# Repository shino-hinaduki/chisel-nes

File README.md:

Chisel NES

=======================

## Demo

TODO:

## HDL Design

TODO:

### 合成手順

#### ChiselNes.v の生成

以下のコマンドでscalaのprojectをビルドして、Chiselから生成したVerilog file  `dst/ChiselNes.v` を得る。

```shell
# sbtが使える環境の場合
$ sbt 'runMain top.ChiselNesDriver --target-dir dst'

# Docker
$ docker-compose run generate
```

#### DE0-CV向けにビルド

`eda/quartusprime_lite_21.1/chisel_nes.qpf` を Quartus Primeで開き、Compile Design を実行して論理合成した後、Program Deviceで書き込む。

(先の手順で生成した `dst/ChiselNes.v` がtop-level design entityに指定されており、プロジェクトにはその他IPや制約ファイルなどが含まれている)

## NES Peripheral EVB for DE0-CV

ファミコンエミュレータを実際のカートリッジで動作させる目的で設計した。

`eda/kicad_6.0.2/nes_peripheral` に、KiCADで設計した基板ファイルがあるので、こちらを参照。

### 機能概要

* DE0-CVのGPIO0,1に直結可能
  * ピンアサインを踏襲していれば、他評価ボード等でも利用可
  * GPIO1からカートリッジとのレベル変換回路をまとめてDisableにすることが可能
* カートリッジとの接続
  * 3.3V - 5V変換付き
  * レベル変換はすべて双方向のため、FPGA側をMaster/Slaveどちらでも利用可能
  * 周辺にプローブ用ピンも引き出し済
* 純正/互換コントローラ接続
  * 3.3V - 5V変換付き
* 純正回路と同じシフトレジスタICを用いたコントローラ入力
  * 3.3Vでプルアップされた入力回路とGNDを公開
  * 純正/互換コントローラの回路とは切替可
* MAX98537を使ったI2S-音声出力回路
* 5Vの外部供給

### ブロック図

```mermaid
graph LR
    GPIO--3.3V CPU/PPU Bus-->TXB0104PW_1
    GPIO--Output Enable-->OutputEnableSelect
    GPIO--5V-->5VSelect
    GPIO-->LED
    GPIO-->UserIO

    DC_Jack--5V-->5VSelect
    5VSelect--5V-->5V
    5V--5V-->CartridgeConnector

    OutputEnableSelect--Output Enable-->TXB0104PW_1
    TXB0104PW_1--5V CPU/PPU Bus-->CartridgeConnector

    GPIO--3.3V ShiftRegister I/O-->TXB0104PW_2
    JoyPadSerialSel-->TXB0104PW_2
    TXB0104PW_2--5V ShiftRegister I/O-->JoyPad0/1_Serial

    JoyPadParallelSel-->4021
    GPIO--3.3V ShiftRegister I/O-->4021
    4021--Parallel IO-->JoyPad0/1_Parallel

    GPIO--I2S-->MAX98357
    MAX98357--Audio Out-->Speaker
    GainSelect-->MAX98357
```

### 回路図

### 部品表

Digikeyで選定した部品を記載。チップコンデンサを始め、サイズ・機能互換であればこれに限らない。また、不要な回路は実装しなくても問題ない
ピンヘッダ、ピンソケットは2.54mm ピッチのものを別途準備すること。

| Ref | Value | 数量 | メーカ製品番号  | url |
| --- | ----  | ---- | --- | ---- |
| C1-C37 |0.1u	| 37 | CL10B104KB8NNWC | https://www.digikey.jp/ja/products/detail/samsung-electro-mechanics/CL10B104KB8NNWC/3887593 |
| C40 | 10p	| 1 | CL10C100CB8NNNC | https://www.digikey.jp/ja/products/detail/samsung-electro-mechanics/CL10C100CB8NNNC/3886727 |
| D1-D3 | LED	| 3 |5988070107F| https://www.digikey.jp/ja/products/detail/dialight/5988070107F/1291269 |
| F1 | Polyfuse_Small	| 1 |0603L300/9SLYR|https://www.digikey.jp/ja/products/detail/littelfuse-inc/0603L300-9SLYR/5427243|
| R1-R22 | 10k	| 22 |RC1608F103CS|https://www.digikey.jp/ja/products/detail/samsung-electro-mechanics/RC1608F103CS/3903493|
| R23	| 0	| 1 |RC0603FR-070RL|https://www.digikey.jp/ja/products/detail/yageo/RC0603FR-070RL/1304008|
| R25, R26 | 100k	| 2 |RC0603JR-07100KL|https://www.digikey.jp/ja/products/detail/yageo/RC0603JR-07100KL/726698|
| U1-U16 | TXB0104PW	| 16 |TXB0104PWR|https://www.digikey.jp/ja/products/detail/texas-instruments/TXB0104PWR/1629102|
| U17, U18 | 4021	| 2 |CD4021BMT|https://www.digikey.jp/ja/products/detail/texas-instruments/CD4021BMT/1690863|
| U19	| MAX98357 | 1 |MAX98357AETE+T|https://www.digikey.jp/ja/products/detail/analog-devices-inc-maxim-integrated/MAX98357AETE-T/4936122|

### GPIO Pin Assign

以下のピンアサインになっているためDE0-CVでなくとも利用可能。GPIO0側の5V,3.3Vは利用していない点に注意

#### GPIO0

|Pin#| GPIO#|KiCad SignalName| Description |
|----|------|----------------|-------------|
|  1 |   D0 |3V3_A11         | CPU Bus |
|  2 |   D1 |3V3_O2          | φ2, System Clock |
|  3 |   D2 |3V3_A10         | CPU Bus |
|  4 |   D3 |3V3_A12         | CPU Bus |
|  5 |   D3 |3V3_A7          | CPU Bus |
|  6 |   D5 |3V3_D7          | CPU Bus |
|  7 |   D6 |3V3_A6          | CPU Bus |
|  8 |   D7 |3V3_D6          | CPU Bus |
|  9 |   D8 |3V3_A3          | CPU Bus |
| 10 |   D9 |3V3_D3          | CPU Bus |
| 11 |   5V |NC              | GPIO0側は未使用 |
| 12 |  GND |GND             |  |
| 13 |  D10 |3V3_A2          | CPU Bus |
| 14 |  D11 |3V3_D2          | CPU Bus |
| 15 |  D12 |3V3_R/~W        | CPU Bus |
| 16 |  D13 |3V3_~ROMSEL     | CPU Bus |
| 17 |  D14 |3V3_~IRQ        | CPU Bus |
| 18 |  D15 |3V3_~WE         | PPU Bus |
| 19 |  D16 |3V3_PA6         | PPU Bus |
| 20 |  D17 |3V3_PA7         | PPU Bus |
| 21 |  D18 |3V3_PA5         | PPU Bus |
| 22 |  D19 |3V3_PA8         | PPU Bus |
| 23 |  D20 |3V3_PA2         | PPU Bus |
| 24 |  D21 |3V3_PA11        | PPU Bus |
| 25 |  D22 |3V3_PA1         | PPU Bus |
| 26 |  D23 |3V3_PA12        | PPU Bus |
| 27 |  D24 |3V3_PD1         | PPU Bus |
| 28 |  D25 |3V3_PD6         | PPU Bus |
| 29 | 3.3V |NC              | GPIO0側は未使用 |
| 30 |  GND |GND             |  |
| 31 |  D26 |3V3_PD2         | PPU Bus |
| 32 |  D27 |3V3_PD5         | PPU Bus |
| 33 |  D28 |3V3_JOY1_P/~S   | 1Player Controller |
| 34 |  D29 |3V3_JOY1_DO     | 1Player Controller |
| 35 |  D30 |3V3_JOY1_RSV    | 1Player Controller |
| 36 |  D31 |3V3_JOY1_CLK    | 1Player Controller |
| 37 |  D32 |3V3_I2S_BCLK    | Audio Codec |
| 38 |  D33 |3V3_I2S_LRCLK   | Audio Codec |
| 39 |  D34 |3V3_I2S_~SD_MODE| Audio Codec |
| 40 |  D35 |3V3_I2S_DIN     | Audio Codec |

#### GPIO1

|Pin#| GPIO#|KiCad SignalName| Description |
|----|------|----------------|-------------|
|  1 |   D0 |3V3_A9          | CPU Bus |
|  2 |   D1 |3V3_A13         | CPU Bus |
|  3 |   D2 |3V3_A8          | CPU Bus |
|  4 |   D3 |3V3_A14         | CPU Bus |
|  5 |   D3 |3V3_A5          | CPU Bus |
|  6 |   D5 |3V3_D5          | CPU Bus |
|  7 |   D6 |3V3_A4          | CPU Bus |
|  8 |   D7 |3V3_D4          | CPU Bus |
|  9 |   D8 |3V3_A1          | CPU Bus |
| 10 |   D9 |3V3_D1          | CPU Bus |
| 11 |   5V |BOARD_5V        | J8 CONN_5VSEL次第で使用する |
| 12 |  GND |GND             |  |
| 13 |  D10 |3V3_A0          | CPU Bus |
| 14 |  D11 |3V3_D0          | CPU Bus |
| 15 |  D12 |3V3_~RD         | PPU Bus |
| 16 |  D13 |3V3_~VRAMCS     | PPU Bus |
| 17 |  D14 |3V3_VRAMA10     | PPU Bus |
| 18 |  D15 |3V3_~PA13       | PPU Bus |
| 19 |  D16 |3V3_PA4         | PPU Bus |
| 20 |  D17 |3V3_PA9         | PPU Bus |
| 21 |  D18 |3V3_PA3         | PPU Bus |
| 22 |  D19 |3V3_PA10        | PPU Bus |
| 23 |  D20 |3V3_PA0         | PPU Bus |
| 24 |  D21 |3V3_PA13        | PPU Bus |
| 25 |  D22 |3V3_PD0         | PPU Bus |
| 26 |  D23 |3V3_PD7         | PPU Bus |
| 27 |  D24 |3V3_PD3         | PPU Bus |
| 28 |  D25 |3V3_PD4         | PPU Bus |
| 29 | 3.3V |3.3V            |  |
| 30 |  GND |GND             |  |
| 31 |  D26 |3V3_RSV0        | 5V側で取り出し可能 |
| 32 |  D27 |3V3_RSV1        | 5V側で取り出し可能 |
| 33 |  D28 |USER_GPIO1      | ピンソケットJ1に引き出し済 |
| 34 |  D29 |USER_LED        | OnBoard LED |
| 35 |  D30 |3V3_JOY2_MICIN  | 2Player Controller |
| 36 |  D31 |USER_GPIO0      | ピンソケットJ1に引き出し済 |
| 37 |  D32 |3V3_JOY2_DO     | 2Player Controller |
| 38 |  D33 |3V3_JOY2_CLK    | 2Player Controller |
| 39 |  D34 |3V3_JOY2_P/~S  | 2Player Controller |
| 40 |  D35 |3V3_OE_IN       | Lowの間はレベル変換をHi-Zで切り離せる |

### 設計データの活用範囲

`eda/kicad_6.0.2/nes_peripheral` にある基板設計データは、 [CC BY-NC 4.0](https://creativecommons.org/licenses/by-nc/4.0/deed) の範囲で利用を許可する。

例えば、本基板の設計データか内容を改変したデータを用い、製造した製品を営利目的で販売する行為は禁止である。

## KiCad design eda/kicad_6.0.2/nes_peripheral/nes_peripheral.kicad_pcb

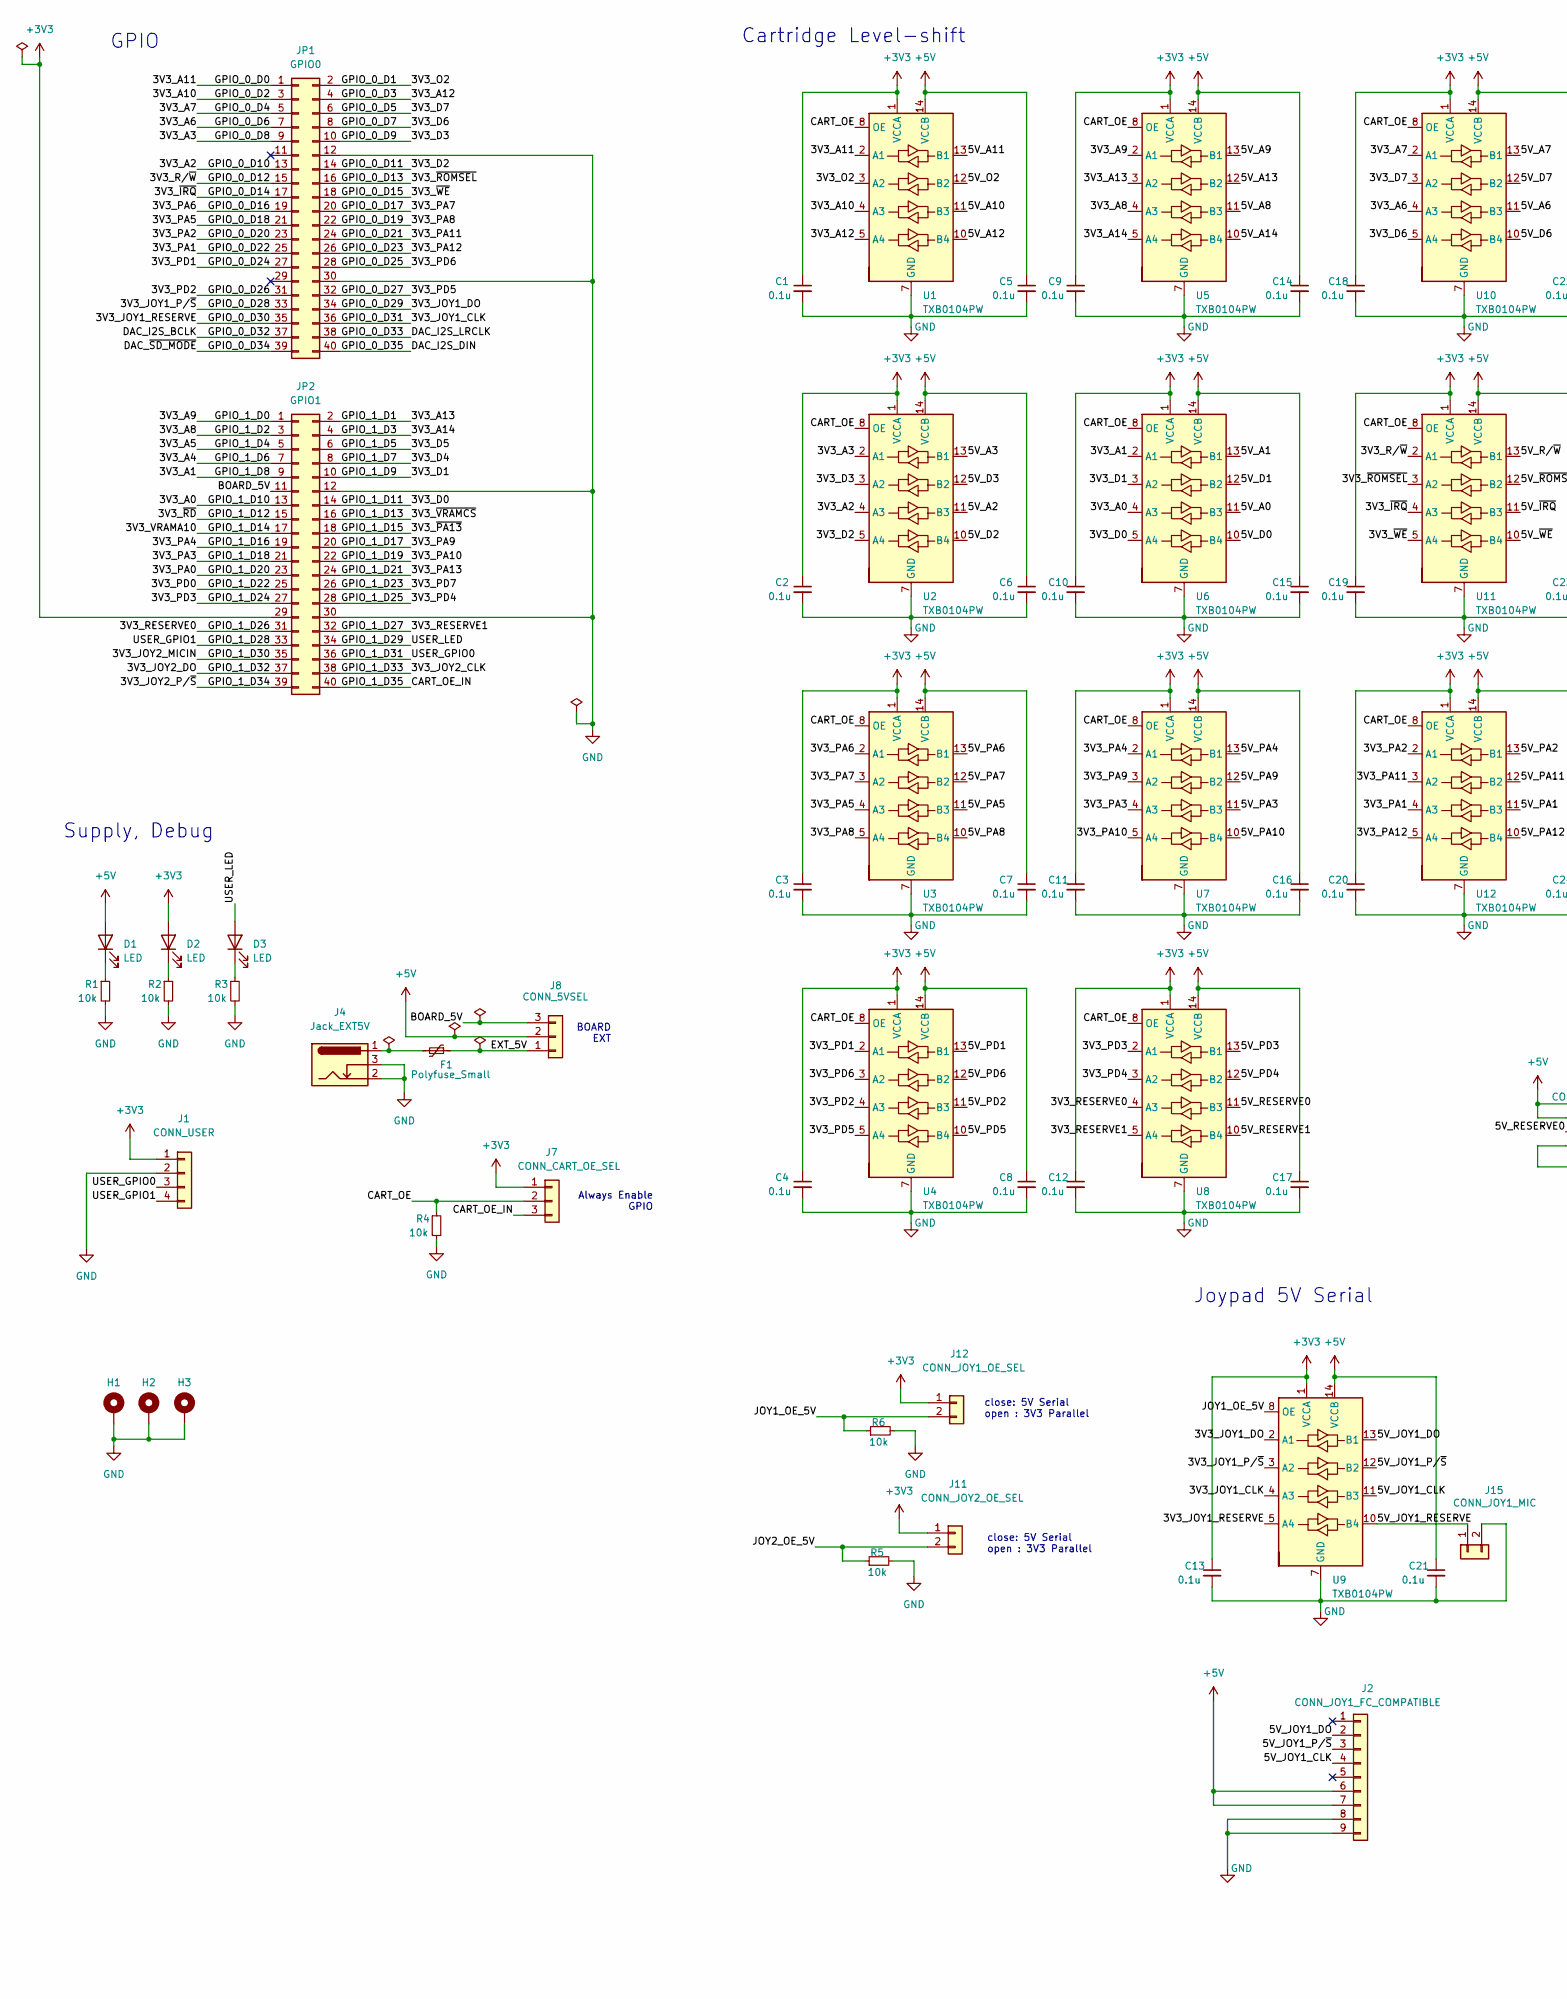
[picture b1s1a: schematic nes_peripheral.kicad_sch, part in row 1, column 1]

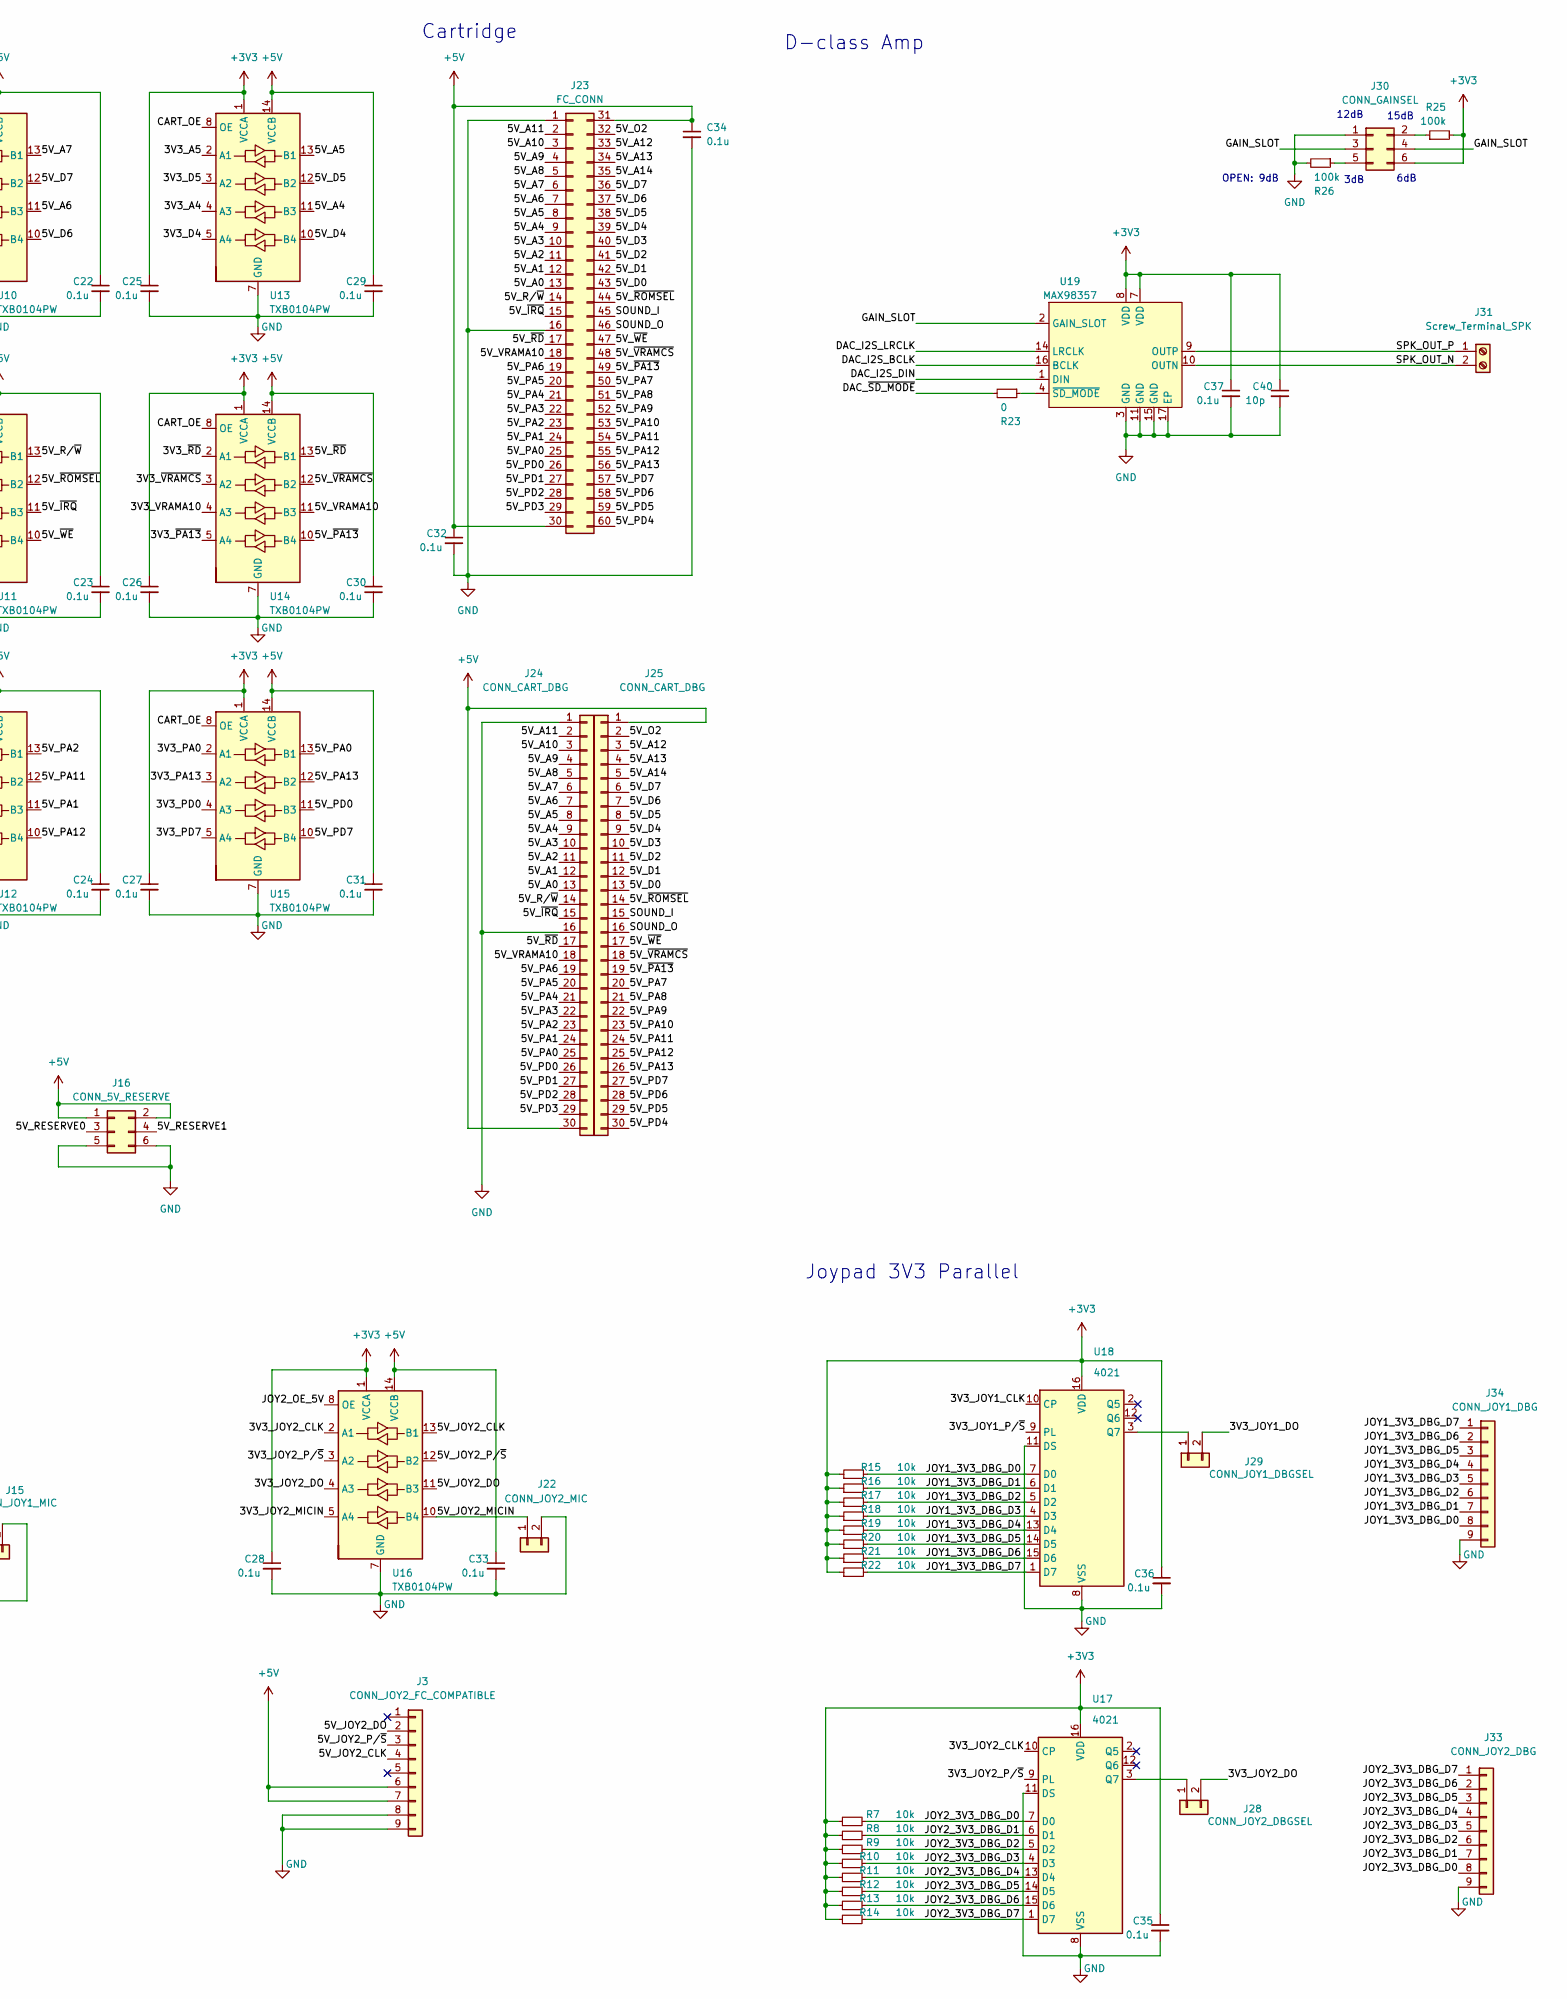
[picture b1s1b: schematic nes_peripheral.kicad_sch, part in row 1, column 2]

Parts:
C1, C2, C3, C4, C5, C6, C7, C8, C9, C10, C11, C12, C13, C14, C15, C16, C17, C18, C19, C20, C21, C22, C23, C24, C25, C26, C27, C28, C29, C30, C31, C32, C33, C34, C35, C36, C37: 0.1u; C_0603_1608Metric_Pad1.08x0.95mm_HandSolder; LCSC C14663
C40: 10p; C_0603_1608Metric_Pad1.08x0.95mm_HandSolder; LCSC C1634
D1, D2, D3: LED; LED_0603_1608Metric_Pad1.05x0.95mm_HandSolder; LCSC C99290
F1: Polyfuse_Small; Fuse_0603_1608Metric_Pad1.05x0.95mm_HandSolder; LCSC C207010
H1, H2, H3: MountingHole_Pad; MountingHole_3.2mm_M3_Pad_TopBottom
J1: CONN_USER; PinSocket_1x04_P2.54mm_Vertical
J2: CONN_JOY1_FC_COMPATIBLE; PinSocket_1x09_P2.54mm_Vertical
J3: CONN_JOY2_FC_COMPATIBLE; PinSocket_1x09_P2.54mm_Vertical
J4: Jack_EXT5V; DCJ3P-14.2X11.0X9.0MM
J7: CONN_CART_OE_SEL; PinHeader_1x03_P2.54mm_Vertical
J8: CONN_5VSEL; PinHeader_1x03_P2.54mm_Vertical
J11: CONN_JOY2_OE_SEL; PinHeader_1x02_P2.54mm_Vertical
J12: CONN_JOY1_OE_SEL; PinHeader_1x02_P2.54mm_Vertical
J15: CONN_JOY1_MIC; PinSocket_1x02_P2.54mm_Vertical
J16: CONN_5V_RESERVE; PinSocket_2x03_P2.54mm_Vertical
J22: CONN_JOY2_MIC; PinSocket_1x02_P2.54mm_Vertical
J23: FC_CONN
J24, J25: CONN_CART_DBG; PinSocket_1x30_P2.54mm_Vertical
J28: CONN_JOY2_DBGSEL; PinHeader_1x02_P2.54mm_Vertical
J29: CONN_JOY1_DBGSEL; PinHeader_1x02_P2.54mm_Vertical
J30: CONN_GAINSEL; PinHeader_2x03_P2.54mm_Vertical
J31: Screw_Terminal_SPK; TerminalBlock_bornier-2_P5.08mm
J33: CONN_JOY2_DBG; PinSocket_1x09_P2.54mm_Vertical
J34: CONN_JOY1_DBG; PinSocket_1x09_P2.54mm_Vertical
JP1: GPIO0; PinSocket_2x20_P2.54mm_Vertical
JP2: GPIO1; PinSocket_2x20_P2.54mm_Vertical
R1, R2, R3, R4, R5, R6, R7, R8, R9, R10, R11, R12, R13, R14, R15, R16, R17, R18, R19, R20, R21, R22: 10k; R_0603_1608Metric_Pad0.98x0.95mm_HandSolder; LCSC C98220
R23: 0; R_0603_1608Metric_Pad0.98x0.95mm_HandSolder; LCSC C95177
R25, R26: 100k; R_0603_1608Metric_Pad0.98x0.95mm_HandSolder; LCSC C100048
U1, U2, U3, U4, U5, U6, U7, U8, U9, U10, U11, U12, U13, U14, U15, U16: TXB0104PW; TSSOP-14_4.4x5mm_P0.65mm; LCSC C60708
U17, U18: 4021; SOIC-16W_5.3x10.2mm_P1.27mm; LCSC C233572
U19: MAX98357; QFN-16_EP_3x3_Pitch0.5mm; LCSC C910544

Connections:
+3V3: C1.1, C2.1, C3.1, C4.1, C9.1, C10.1, C11.1, C12.1, C13.1, C18.1, C19.1, C20.1, C25.1, C26.1, C27.1, C28.1, C35.1, C36.1, C37.1, C40.1, D2.2 (A), J1.1, J7.1, J11.1, J12.1, J30.6, JP2.29, R7.1, R8.1, R9.1, R10.1, R11.1, R12.1, R13.1, R14.1, R15.1, R16.1, R17.1, R18.1, R19.1, R20.1, R21.1, R22.1, R25.2, U1.1 (VCCA), U2.1 (VCCA), U3.1 (VCCA), U4.1 (VCCA), U5.1 (VCCA), U6.1 (VCCA), U7.1 (VCCA), U8.1 (VCCA), U9.1 (VCCA), U10.1 (VCCA), U11.1 (VCCA), U12.1 (VCCA), U13.1 (VCCA), U14.1 (VCCA), U15.1 (VCCA), U16.1 (VCCA), U17.16 (VDD), U18.16 (VDD), U19.7 (VDD), U19.8 (VDD)
+5V: C5.1, C6.1, C7.1, C8.1, C14.1, C15.1, C16.1, C17.1, C21.1, C22.1, C23.1, C24.1, C29.1, C30.1, C31.1, C32.1, C33.1, C34.1, D1.2 (A), J2.6, J2.7, J3.6, J3.7, J8.2, J16.1, J16.2, J23.30, J23.31, J24.30, J25.1, U1.14 (VCCB), U2.14 (VCCB), U3.14 (VCCB), U4.14 (VCCB), U5.14 (VCCB), U6.14 (VCCB), U7.14 (VCCB), U8.14 (VCCB), U9.14 (VCCB), U10.14 (VCCB), U11.14 (VCCB), U12.14 (VCCB), U13.14 (VCCB), U14.14 (VCCB), U15.14 (VCCB), U16.14 (VCCB)
/3V3_A0: JP2.13, U6.4 (A3)
/3V3_A1: JP2.9, U6.2 (A1)
/3V3_A2: JP1.13, U2.4 (A3)
/3V3_A3: JP1.9, U2.2 (A1)
/3V3_A4: JP2.7, U13.4 (A3)
/3V3_A5: JP2.5, U13.2 (A1)
/3V3_A6: JP1.7, U10.4 (A3)
/3V3_A7: JP1.5, U10.2 (A1)
/3V3_A8: JP2.3, U5.4 (A3)
/3V3_A9: JP2.1, U5.2 (A1)
/3V3_A10: JP1.3, U1.4 (A3)
/3V3_A11: JP1.1, U1.2 (A1)
/3V3_A12: JP1.4, U1.5 (A4)
/3V3_A13: JP2.2, U5.3 (A2)
/3V3_A14: JP2.4, U5.5 (A4)
/3V3_D0: JP2.14, U6.5 (A4)
/3V3_D1: JP2.10, U6.3 (A2)
/3V3_D2: JP1.14, U2.5 (A4)
/3V3_D3: JP1.10, U2.3 (A2)
/3V3_D4: JP2.8, U13.5 (A4)
/3V3_D5: JP2.6, U13.3 (A2)
/3V3_D6: JP1.8, U10.5 (A4)
/3V3_D7: JP1.6, U10.3 (A2)
/3V3_JOY1_CLK: JP1.36, U9.4 (A3), U18.10 (CP)
/3V3_JOY1_DO: J29.2, JP1.34, U9.2 (A1)
/3V3_JOY1_P/~S: JP1.33, U9.3 (A2), U18.9 (PL)
/3V3_JOY1_RESERVE: JP1.35, U9.5 (A4)
/3V3_JOY2_CLK: JP2.38, U16.2 (A1), U17.10 (CP)
/3V3_JOY2_DO: J28.2, JP2.37, U16.4 (A3)
/3V3_JOY2_MICIN: JP2.35, U16.5 (A4)
/3V3_JOY2_P/~S: JP2.39, U16.3 (A2), U17.9 (PL)
/3V3_O2: JP1.2, U1.3 (A2)
/3V3_PA0: JP2.23, U15.2 (A1)
/3V3_PA1: JP1.25, U12.4 (A3)
/3V3_PA2: JP1.23, U12.2 (A1)
/3V3_PA3: JP2.21, U7.4 (A3)
/3V3_PA4: JP2.19, U7.2 (A1)
/3V3_PA5: JP1.21, U3.4 (A3)
/3V3_PA6: JP1.19, U3.2 (A1)
/3V3_PA7: JP1.20, U3.3 (A2)
/3V3_PA8: JP1.22, U3.5 (A4)
/3V3_PA9: JP2.20, U7.3 (A2)
/3V3_PA10: JP2.22, U7.5 (A4)
/3V3_PA11: JP1.24, U12.3 (A2)
/3V3_PA12: JP1.26, U12.5 (A4)
/3V3_PA13: JP2.24, U15.3 (A2)
/3V3_PD0: JP2.25, U15.4 (A3)
/3V3_PD1: JP1.27, U4.2 (A1)
/3V3_PD2: JP1.31, U4.4 (A3)
/3V3_PD3: JP2.27, U8.2 (A1)
/3V3_PD4: JP2.28, U8.3 (A2)
/3V3_PD5: JP1.32, U4.5 (A4)
/3V3_PD6: JP1.28, U4.3 (A2)
/3V3_PD7: JP2.26, U15.5 (A4)
/3V3_RESERVE0: JP2.31, U8.4 (A3)
/3V3_RESERVE1: JP2.32, U8.5 (A4)
/3V3_R/~W: JP1.15, U11.2 (A1)
/3V3_VRAMA10: JP2.17, U14.4 (A3)
/3V3_~IRQ: JP1.17, U11.4 (A3)
/3V3_~PA13: JP2.18, U14.5 (A4)
/3V3_~RD: JP2.15, U14.2 (A1)
/3V3_~ROMSEL: JP1.16, U11.3 (A2)
/3V3_~VRAMCS: JP2.16, U14.3 (A2)
/3V3_~WE: JP1.18, U11.5 (A4)
/5V_A0: J23.13, J24.13, U6.11 (B3)
/5V_A1: J23.12, J24.12, U6.13 (B1)
/5V_A2: J23.11, J24.11, U2.11 (B3)
/5V_A3: J23.10, J24.10, U2.13 (B1)
/5V_A4: J23.9, J24.9, U13.11 (B3)
/5V_A5: J23.8, J24.8, U13.13 (B1)
/5V_A6: J23.7, J24.7, U10.11 (B3)
/5V_A7: J23.6, J24.6, U10.13 (B1)
/5V_A8: J23.5, J24.5, U5.11 (B3)
/5V_A9: J23.4, J24.4, U5.13 (B1)
/5V_A10: J23.3, J24.3, U1.11 (B3)
/5V_A11: J23.2, J24.2, U1.13 (B1)
/5V_A12: J23.33, J25.3, U1.10 (B4)
/5V_A13: J23.34, J25.4, U5.12 (B2)
/5V_A14: J23.35, J25.5, U5.10 (B4)
/5V_D0: J23.43, J25.13, U6.10 (B4)
/5V_D1: J23.42, J25.12, U6.12 (B2)
/5V_D2: J23.41, J25.11, U2.10 (B4)
/5V_D3: J23.40, J25.10, U2.12 (B2)
/5V_D4: J23.39, J25.9, U13.10 (B4)
/5V_D5: J23.38, J25.8, U13.12 (B2)
/5V_D6: J23.37, J25.7, U10.10 (B4)
/5V_D7: J23.36, J25.6, U10.12 (B2)
/5V_JOY1_CLK: J2.4, U9.11 (B3)
/5V_JOY1_DO: J2.2, U9.13 (B1)
/5V_JOY1_P/~S: J2.3, U9.12 (B2)
/5V_JOY1_RESERVE: J15.1, U9.10 (B4)
/5V_JOY2_CLK: J3.4, U16.13 (B1)
/5V_JOY2_DO: J3.2, U16.11 (B3)
/5V_JOY2_MICIN: J22.1, U16.10 (B4)
/5V_JOY2_P/~S: J3.3, U16.12 (B2)
/5V_O2: J23.32, J25.2, U1.12 (B2)
/5V_PA0: J23.25, J24.25, U15.13 (B1)
/5V_PA1: J23.24, J24.24, U12.11 (B3)
/5V_PA2: J23.23, J24.23, U12.13 (B1)
/5V_PA3: J23.22, J24.22, U7.11 (B3)
/5V_PA4: J23.21, J24.21, U7.13 (B1)
/5V_PA5: J23.20, J24.20, U3.11 (B3)
/5V_PA6: J23.19, J24.19, U3.13 (B1)
/5V_PA7: J23.50, J25.20, U3.12 (B2)
/5V_PA8: J23.51, J25.21, U3.10 (B4)
/5V_PA9: J23.52, J25.22, U7.12 (B2)
/5V_PA10: J23.53, J25.23, U7.10 (B4)
/5V_PA11: J23.54, J25.24, U12.12 (B2)
/5V_PA12: J23.55, J25.25, U12.10 (B4)
/5V_PA13: J23.56, J25.26, U15.12 (B2)
/5V_PD0: J23.26, J24.26, U15.11 (B3)
/5V_PD1: J23.27, J24.27, U4.13 (B1)
/5V_PD2: J23.28, J24.28, U4.11 (B3)
/5V_PD3: J23.29, J24.29, U8.13 (B1)
/5V_PD4: J23.60, J25.30, U8.12 (B2)
/5V_PD5: J23.59, J25.29, U4.10 (B4)
/5V_PD6: J23.58, J25.28, U4.12 (B2)
/5V_PD7: J23.57, J25.27, U15.10 (B4)
/5V_RESERVE0: J16.3, U8.11 (B3)
/5V_RESERVE1: J16.4, U8.10 (B4)
/5V_R/~W: J23.14, J24.14, U11.13 (B1)
/5V_VRAMA10: J23.18, J24.18, U14.11 (B3)
/5V_~IRQ: J23.15, J24.15, U11.11 (B3)
/5V_~PA13: J23.49, J25.19, U14.10 (B4)
/5V_~RD: J23.17, J24.17, U14.13 (B1)
/5V_~ROMSEL: J23.44, J25.14, U11.12 (B2)
/5V_~VRAMCS: J23.48, J25.18, U14.12 (B2)
/5V_~WE: J23.47, J25.17, U11.10 (B4)
/BOARD_5V: J8.3, JP2.11
/CART_OE: J7.2, R4.1, U1.8 (OE), U2.8 (OE), U3.8 (OE), U4.8 (OE), U5.8 (OE), U6.8 (OE), U7.8 (OE), U8.8 (OE), U10.8 (OE), U11.8 (OE), U12.8 (OE), U13.8 (OE), U14.8 (OE), U15.8 (OE)
/CART_OE_IN: J7.3, JP2.40
/DAC_I2S_BCLK: JP1.37, U19.16 (BCLK)
/DAC_I2S_DIN: JP1.40, U19.1 (DIN)
/DAC_I2S_LRCLK: JP1.38, U19.14 (LRCLK)
/DAC_~SD_MODE: JP1.39, R23.2
/EXT_5V: F1.1, J8.1
/GAIN_SLOT: J30.3, J30.4, U19.2 (GAIN_SLOT)
/GPIO_1_D28: J1.4, JP2.33
/GPIO_1_D29: D3.2 (A), JP2.34
/GPIO_1_D31: J1.3, JP2.36
/JOY1_3V3_DBG_D0: J34.8, R15.2, U18.7 (D0)
/JOY1_3V3_DBG_D1: J34.7, R16.2, U18.6 (D1)
/JOY1_3V3_DBG_D2: J34.6, R17.2, U18.5 (D2)
/JOY1_3V3_DBG_D3: J34.5, R18.2, U18.4 (D3)
/JOY1_3V3_DBG_D4: J34.4, R19.2, U18.13 (D4)
/JOY1_3V3_DBG_D5: J34.3, R20.2, U18.14 (D5)
/JOY1_3V3_DBG_D6: J34.2, R21.2, U18.15 (D6)
/JOY1_3V3_DBG_D7: J34.1, R22.2, U18.1 (D7)
/JOY1_OE_5V: J12.2, R6.1, U9.8 (OE)
/JOY2_3V3_DBG_D0: J33.8, R7.2, U17.7 (D0)
/JOY2_3V3_DBG_D1: J33.7, R8.2, U17.6 (D1)
/JOY2_3V3_DBG_D2: J33.6, R9.2, U17.5 (D2)
/JOY2_3V3_DBG_D3: J33.5, R10.2, U17.4 (D3)
/JOY2_3V3_DBG_D4: J33.4, R11.2, U17.13 (D4)
/JOY2_3V3_DBG_D5: J33.3, R12.2, U17.14 (D5)
/JOY2_3V3_DBG_D6: J33.2, R13.2, U17.15 (D6)
/JOY2_3V3_DBG_D7: J33.1, R14.2, U17.1 (D7)
/JOY2_OE_5V: J11.2, R5.1, U16.8 (OE)
/SOUND_I: J23.45, J25.15
/SOUND_O: J23.46, J25.16
/SPK_OUT_N: J31.2, U19.10 (OUTN)
/SPK_OUT_P: J31.1, U19.9 (OUTP)
GND: C1.2, C2.2, C3.2, C4.2, C5.2, C6.2, C7.2, C8.2, C9.2, C10.2, C11.2, C12.2, C13.2, C14.2, C15.2, C16.2, C17.2, C18.2, C19.2, C20.2, C21.2, C22.2, C23.2, C24.2, C25.2, C26.2, C27.2, C28.2, C29.2, C30.2, C31.2, C32.2, C33.2, C34.2, C35.2, C36.2, C37.2, C40.2, H1.1, H2.1, H3.1, J1.2, J2.8, J2.9, J3.8, J3.9, J4.2, J4.3, J15.2, J16.5, J16.6, J22.2, J23.1, J23.16, J24.1, J24.16, J30.1, J33.9, J34.9, JP1.12, JP1.30, JP2.12, JP2.30, R1.2, R2.2, R3.2, R4.2, R5.2, R6.2, R26.2, U1.7 (GND), U2.7 (GND), U3.7 (GND), U4.7 (GND), U5.7 (GND), U6.7 (GND), U7.7 (GND), U8.7 (GND), U9.7 (GND), U10.7 (GND)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
unnamed: D1.1 (K), R1.1
unnamed: D2.1 (K), R2.1
unnamed: D3.1 (K), R3.1
unnamed: F1.2, J4.1
unnamed: J28.1, U17.3 (Q7)
unnamed: J29.1, U18.3 (Q7)
unnamed: J30.2, R25.1
unnamed: J30.5, R26.1
unnamed: R23.1, U19.4 (~SD_MODE)

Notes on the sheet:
D-class Amp
Joypad 5V Serial
12dB
Supply, Debug
close: 5V Serial open : 3V3 Parallel
Cartridge
3dB
Cartridge Level-shift
GPIO
Always Enable GPIO
BOARD EXT
OPEN: 9dB
Joypad 3V3 Parallel
6dB
15dB

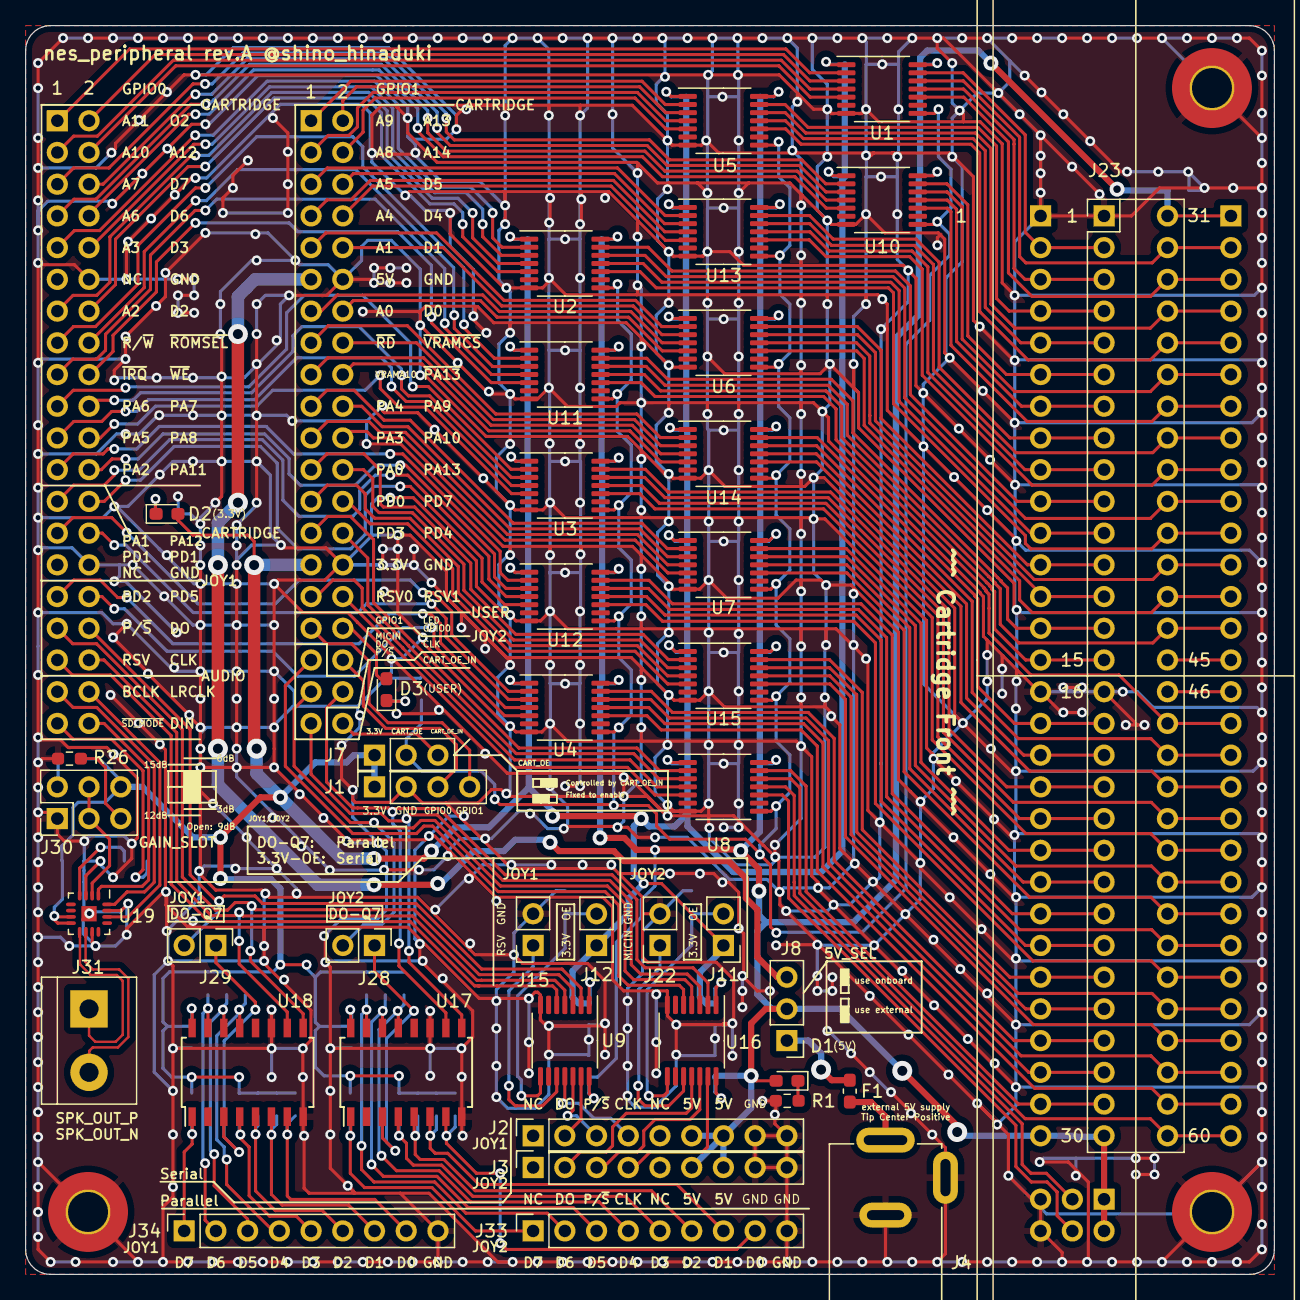
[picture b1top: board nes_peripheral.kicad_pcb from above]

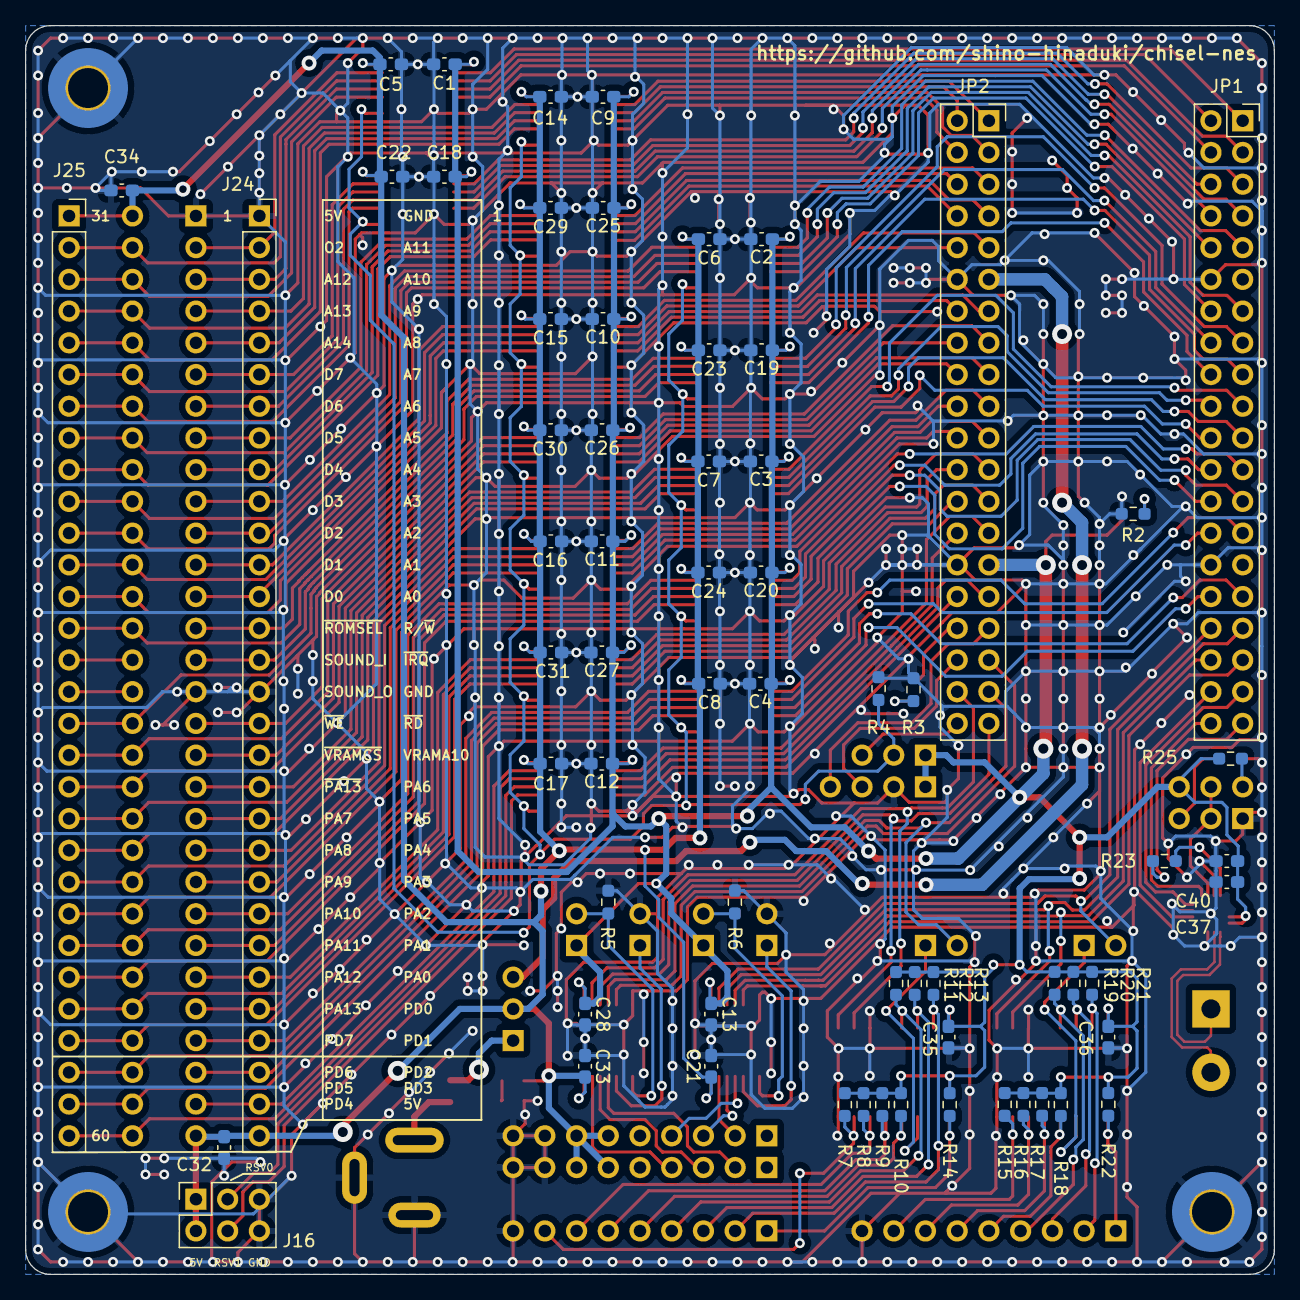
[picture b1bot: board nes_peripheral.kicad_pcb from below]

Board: 2 copper layers, 100.0 x 100.0 mm, 111 parts (66 on the bottom side), 174 nets.

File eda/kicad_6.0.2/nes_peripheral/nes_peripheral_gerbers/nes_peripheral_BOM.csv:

Comment,Designator,Footprint,LCSC
"0.1u","C1,C2,C3,C4,C5,C6,C7,C8,C9,C10,C11,C12,C13,C14,C15,C16,C17,C18,C19,C20,C21,C22,C23,C24,C25,C26,C27,C28,C29,C30,C31,C32,C33,C34,C35,C36,C37","Capacitor_SMD:C_0603_1608Metric_Pad1.08x0.95mm_HandSolder","C14663"
"10p","C40","Capacitor_SMD:C_0603_1608Metric_Pad1.08x0.95mm_HandSolder","C1634"
"LED","D1,D2,D3","LED_SMD:LED_0603_1608Metric_Pad1.05x0.95mm_HandSolder","C99290"
"Polyfuse_Small","F1","Fuse:Fuse_0603_1608Metric_Pad1.05x0.95mm_HandSolder","C207010"
"10k","R1,R2,R3,R4,R5,R6,R7,R8,R9,R10,R11,R12,R13,R14,R15,R16,R17,R18,R19,R20,R21,R22","Resistor_SMD:R_0603_1608Metric_Pad0.98x0.95mm_HandSolder","C98220"
"0","R23","Resistor_SMD:R_0603_1608Metric_Pad0.98x0.95mm_HandSolder","C95177"
"100k","R25,R26","Resistor_SMD:R_0603_1608Metric_Pad0.98x0.95mm_HandSolder","C100048"
"TXB0104PW","U1,U2,U3,U4,U5,U6,U7,U8,U9,U10,U11,U12,U13,U14,U15,U16","Package_SO:TSSOP-14_4.4x5mm_P0.65mm","C60708"
"4021","U17,U18","Package_SO:SOIC-16W_5.3x10.2mm_P1.27mm","C233572"
"MAX98357","U19","nes_peripheral:QFN-16_EP_3x3_Pitch0.5mm","C910544"

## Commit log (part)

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2022-01-15 Template cleanup
2022-01-15 add: docker-compose.yml
2022-01-15 fix: CI fail #2 https://github.com/shino-hinaduki/chisel-nes/runs/4827396784?check_suite_focus=true
2022-01-15 refactor: install scalafmt
2022-01-15 wip: VirtualCartのCpuBusを実装
2022-01-16 fix: typo
2022-01-17 feat: VirtualCartの読み書きを実装
2022-01-17 refactor: format適用
2022-01-17 feat: .NES Fileの読み込みを実装
2022-01-17 refactor: fix comment
2022-01-18 現状仕様が曖昧な箇所を削除
2022-01-18 feat: WRAMを実装
2022-01-18 test: WorkRamSpecにR/Wパターンを追加
2022-01-19 test: 飛び飛びにWriteするパターンを追加
2022-01-19 env: .vscodeのファイルを追加
2022-01-19 refactor: NesFileを分離
2022-01-19 CpuRegを定義
2022-01-19 feat: Verilog出力を実装
2022-01-19 env: CIにverilog出力を追加
2022-01-20 refactor: WRAM,VRAMは同じ素子なので共通化
2022-01-20 refactor: コメント追加
2022-01-20 feat: VRAM,WRAM追加
2022-01-20 feat: Decoder.scalaを追加
2022-01-21 feat: Decoderを実装
2022-01-22 test: DecoderSpecを実装
2022-01-22 feat: BusSelectorを実装
2022-01-22 fix: Moduleのinstance方法が間違っていたので修正
2022-01-22 test: BusSelectorのテストケースを作成
2022-01-22 refactor: scalafmt実施、nGをnEnにリネーム
2022-01-22 env: millのテストを除外
2022-01-22 env: docker-composeでverilog吐き出せるようにした
2022-01-22 refactor: warning抑制
2022-01-23 feat: TriState/TriStateBufferを実装
2022-01-23 test: TriStateBufferTestを実装
2022-01-23 fix: Ram.dataOutをTriStateに対応させた
2022-01-23 fix: InvertBufferの出力論理を修正
2022-01-23 comment: InvertBufferの説明を修正
2022-01-23 comment: 真理値表を修正
2022-01-23 feat: ShiftRegisterを実装
2022-01-23 test: ShiftRegisterの最小ケースを実装
2022-01-23 test: パラレル入力のテストを実装
2022-01-23 test: Parallel input testでparallel入力にかけるclock数を降ったパターンを追加
2022-01-24 fix: RamのWrite時にdataOutをドライブしていたので修正
2022-01-24 refactor: コメント修正
2022-01-25 feat: IFを実装
2022-01-25 fix: RegをRegInitにして初期値を入れるようにした
2022-01-27 feat: InstructionFetchを仮実装
2022-01-27 feat: Addressing, Instructionの定義を追加
2022-01-27 refactor: package構成を整理
2022-01-27 wip: IF/ID実装中
2022-01-29 wip: クラス構成を整理。コメント追加
2022-01-29 Create LICENSE
2022-01-29 refactor: クラス整理中。port名修正
2022-01-29 feat: CPU内部のBusArbiterを実装
2022-01-29 fix: 合成できない問題を修正
2022-01-29 fix: dataOutRegがInvalid担っていた問題を修正
2022-01-29 test: Writeするテストを作成
2022-01-29 refactor: 初期化部分を切り出し
2022-01-29 test: 読み書きのポートを分けたケースを追加
2022-01-29 test: Read/Writeを同時に要求したケースを追加
2022-01-30 test: Busが調停されるケースを追加
2022-01-30 test: 3port使った調停を動作確認
2022-01-30 test: Fetchの最低限のパターンを作成
2022-01-30 test: 複数要求並べたケースを作成
2022-01-31 fix: Fetch完了時にBusを握りっぱなしになる挙動を修正
2022-02-01 fix: discardの要因を削除、BusyRegの追加
2022-02-02 test: Single fetch verificationのテストを修正
2022-02-02 test: Sequential fetch verificationを有効化
2022-02-02 fix: busyの信号生成に!=を使っていて正しく動いていなかった点を修正
2022-02-02 test: IR破棄するパターンを追加
2022-02-03 test: データ破棄の動作確認
2022-02-03 test: Busに待たされるケースを追加
2022-02-03 test: 一通り流すパターンを追加
2022-02-03 test: readStrobe+discardを同時に要求し続けるケースを追加
2022-02-04 refactor: InstructionFetchにリネーム
2022-02-04 wip: DecodeSpecを作成
2022-02-04 refactor: 複数パターンのテストの記述を是正
2022-02-04 refactor: InstructionDecodeにリネーム
2022-02-04 fix: opcode対応表を修正
2022-02-05 feat: DE0-CVのプロジェクトを作成
2022-02-05 wip: virtualjtagのIPを追加
2022-02-06 wip: TopModule用のクラス作成中
2022-02-06 feat: ChiselNes.scalaにボード動作確認の実装を追加
2022-02-07 refactor: BusArbiterのパッケージを移動
2022-02-07 feat: PlatformDesignerでJtagDebug用デザイン作成
2022-02-08 wip: OperandFetchのIO定義を追加
2022-02-08 wip: OF実装中
2022-02-09 wip: OFのROMから読み出す部分をリファクタリングして実装
2022-02-09 refactor: AddressingModeの定義名を修正
2022-02-09 wip: OFの実装を整理
2022-02-11 fix: 検証用に期待値がない箇所をDon't careに置き換え
2022-02-11 refactor: BusSlavePortをBusIOにリネーム
2022-02-11 refactor: ExternalIOをBoardIOにリネーム
2022-02-11 env: diagram出力に対応
2022-02-11 refactor: cpu内のsubpackageを簡略化
2022-02-11 fix: import文のroot参照を修正
2022-02-11 env: trainingCommasをkeepに設定
2022-02-11 feat: Immediate, Absoute, Implied, Accumulateを実装
2022-02-12 refactor: OFから共通定義を切り出し
2022-02-12 refactor: BusIOの名前空間を変更
2022-02-12 env: scaladocを追加
2022-02-12 wip: OperandFetchImplに実実装を分解中
2022-02-12 feat: AccumulatorImplを実装
2022-02-12 feat: Immediate,Accumulator,Absoluteを実装
2022-02-12 feat: ZeroPageを実装。引数をリファクタリング
2022-02-12 refactor: addressing.Processを別ファイルに切り出し
2022-02-12 feat: Indexed Absoluteを実装
2022-02-12 fix: IndexedAbsoluteのaddressingで返す値の分岐漏れを修正
2022-02-12 feat: IndexedZeroPageを実装
2022-02-12 feat: Indirectを実装
2022-02-12 feat: IndexedIndirectを実装
2022-02-12 feat: IndirectIndexdを実装
2022-02-12 refactor: OperandFetchImpl -> AddressingImplにリネーム
2022-02-12 refactor: 引数順を入れかえ
2022-02-12 refactor: readAddrが未使用だったので削除
2022-02-12 refactor: AddressingImplの引数を整理
2022-02-12 feat: OFの実装をAddressingImpl定義を使ったものに修正
2022-02-12 fix: ReadDataで間違って結果を消していた
2022-02-13 test: ID test 0x00 ~ 0x0fを追加
2022-02-13 test: ID 1xのテストを追加
2022-02-13 test: ID 2xのテスト追加
2022-02-13 fix: opcode=0x2b ANC Immを追加
2022-02-13 test: ID 3xのテストを追加
2022-02-13 test: ID 4xのテストを追加
2022-02-13 test: ID 6xのテストを追加
2022-02-13 test: ID 7xのテストを追加
2022-02-13 test: Id 8xのテストを追加
2022-02-13 fix: sbxをaxsにリネーム, xaaを追加
2022-02-13 test: ID 9xのテストを追加
2022-02-13 fix: 0x93,0x9b,0x9c,0x9e,0x9fのundocumented命令を追加
2022-02-13 test: ID axのテストを追加
2022-02-13 fix: 0xab LAX Immediateを追加
2022-02-13 env: add .gitattributes
2022-02-13 fix: ディレクトリ構成を修正
2022-02-13 test: ID bxのテストを追加
2022-02-13 fix: 0xbb LAS YIndexedAbsoluteを追加
2022-02-13 test: ID exのテストを追加
2022-02-13 test: InstructionDecodeのTableを一通り確認
2022-02-13 feat: OF時のMemRead用非判定を実装
2022-02-13 fix: inc,inx,inyが漏れていたので修正、コメント初歌
2022-02-13 refactor: 関数名を修正
2022-02-14 feat: Index reg参照するAddressingの結果報告を遅らせるモードを実装
2022-02-15 fix: DataFetch判定が一部誤っていたので修正
2022-02-15 test: DataFetch有無のテスト期待値を修正
2022-02-16 refactor: debug->cartに名前空間を変更
2022-02-18 wip: 拡張基板プロジェクト追加
2022-02-18 feat: レベル変換の回路図を作成
2022-02-18 feat: GPIO0/1のアサイン決定
2022-02-19 feat: MAX98357 のシンボル追加
2022-02-19 feat: デバッグピン・コントローラの回路を追加
2022-02-19 feat: コントローラのパラレル入力でバッグ回路を追加
2022-02-20 fix: ERCを通した
2022-02-20 feat: max98357のフットプリントを追加
2022-02-20 feat: FC_CONNのfootprintを作成
2022-02-20 wip: 基板配置検討中
2022-02-21 feat: レベル変換回路を引ききった
2022-02-22 feat: 残りの部品配置を修正中
2022-02-23 wip: 電源配線中
2022-02-23 fix: I2Sのピン配置を変更
2022-02-23 feat: コントローラの3V3パラレル配線を追加
2022-02-24 feat: 音声出力回路をモノラルに変更、配線を修正
2022-02-26 feat: コントローラ用回路を引いた
2022-02-26 feat: 3.3Vを配線
2022-02-27 feat: 配線終わり
2022-02-27 feat: DRC通した
2022-02-27 feat: 表面のシルクを整備
2022-02-28 feat: シルク表裏整備
2022-03-01 feat: 製造ファイル出力
2022-03-02 doc: BOMを記載
2022-03-02 doc: tableの体裁を修正
2022-03-02 doc: 部品数量を修正
2022-03-02 doc: READMEに画像を追加
2022-03-02 doc: Licenseファイルを追加
2022-03-02 fix: 画像パスを修正
2022-03-03 doc: ブロック図を追加
2022-03-05 wip: デバッグ用プロジェクト追加
2022-03-05 env: ディレクトリ構成を修正
2022-03-06 feat: PCB Assembly用造ファイルを追加
2022-03-06 fix: BOMを実装部品のみにした
2022-03-06 feat: MahApps.Metro導入
2022-03-06 feat: themeの変更方法を確認
2022-03-07 feat: UT考え中
2022-03-08 env: Core, Core.Testのサブプロジェクトを作成
2022-03-08 wip: JtagMaster実装中
2022-03-08 feat: IJtagCommunicatableを作成
2022-03-09 wip: JtagMaster実装中
2022-03-10 refactor: code formatを変更
2022-03-10 refactor: .editorconfigを作成
2022-03-10 refactor: 名前空間を修正
2022-03-10 refactor: byte配列の変換にはBitConverterを使う
2022-03-10 wip: 動作確認中
2022-03-10 feat: IDCODE読み取りを動作確認できた
2022-03-13 wip: UIデザイン修正中
2022-03-13 refactor: 処理手順をリファクタリング
2022-03-13 refactor: リファクタしたけど治らん
2022-03-13 feat: PULSE_NCONFIG を実装
2022-03-14 refactor: 処理を簡略化
2022-03-14 feat: Usercode読み出しを実装
2022-03-17 wip: DebugAccessPort classの雛形を作成
2022-03-19 wip: VJtag考え中
2022-03-19 feat: VJTAG実装の雛形と、VIRのキャプチャを実装
2022-03-19 refactor: VirtualInstructionをBundleに置き換え
2022-03-19 refactor: VJTAG関連をboard packageに移動
2022-03-19 feat: VirtualJtagBridgeをtop moduleに追加。その際のエラーを修正
2022-03-20 feat: 7segにVIRを表示するように変更
2022-03-20 feat: VJTAG用デザインでビルド
2022-03-20 feat: VJTAGで命令の流し込みの動作確認ができた
2022-03-20 test: VDRの読み出しもテストに追加
2022-03-21 feat: Shift-DR制御の追加
2022-03-21 test: 合成してTestInvalidUserInstを流して、右1シフト分足らないことを確認 expect: 0xa5, actuall: 0x4a (0x80 | (0x4a >> 1) で期待値になる)
2022-03-22 fix: DataKind=0x7fもInvalid扱いにした
2022-03-22 fix: Shift-DRで読み出せる値が1bit遅れて出てくる問題を修正
2022-03-22 feat: DPRAM, FIFO, PLL周りのIPを追加
2022-03-23 feat: async_fifo_dap_to_jtagを追加
2022-03-23 refactor: JTAG関連の名前空間を修正
2022-03-23 refactor: dap_tp_vjtagに改名
2022-03-23 feat: AsyncFifoのBlackBox定義を追加
2022-03-23 feat: PLL関連の定義を追加
2022-03-23 feat: VirtualJtagの定義を追加
2022-03-23 feat: virtual_jtagをchisel内に収めた
2022-03-23 feat: 8f2810ceec663 のデザインで合成して動作確認
2022-03-23 wip: VideoOut関連の定義を追加
2022-03-23 Revert "refactor: JTAG関連の名前空間を修正"
    This reverts commit 3469af89d6a7632666a9ab0368e20e6f50f08db1.
2022-03-24 fix: 重複したwithClockを削除
2022-03-24 feat: gpio_bidirectionalを追加
2022-03-24 refactor: ChiselNes.scalaの生成物を直接top moduleに据え置き
2022-03-24 feat: 7seg decodeが複数箇所に散らかっていたのでmodule化した
2022-03-24 feat: チャタリング除去モジュールを追加
2022-03-24 fix: 合成が通らなかったので修正
2022-03-25 fix: FBのアドレス範囲を修正
2022-03-25 feat: VgaOutを実装
2022-03-25 fix: FBのscaling未対応だったので修正
2022-03-26 feat: board.ram.typesにDPRAM系の定義を追加
2022-03-26 refactor: FrameBufferIOの定義をRAMアクセス用の定義で置き換え
2022-03-26 refactor: Port名を整理
2022-03-26 refactor: AsnycFIFOのIO定義名を変更
2022-03-26 wip: R/W cmdの定義変更前
2022-03-26 feat: DebugAccess用コマンド定義を修正
2022-03-26 feat: DebugAccessCommandの受付を実装
2022-03-26 fix: VJTAG to DAPのAsyncFIFOの設定を修正
2022-03-26 fix: DAP to JVTAGのAsyncFIFO設定を修正
2022-03-26 fix: aclrはFIFOのEnq/Deq I/F定義からは削除
2022-03-27 refactor: 体裁を修正
2022-03-27 fix: vjtag-dap間のアドレスを4byte単位で扱うのでサイズ修正
2022-03-27 feat: VirtualJtagBridgeのdataRegを32bit化
2022-03-27 test: invalid cmdを投げて0x665599aaが変えることを確認
2022-03-27 refactor: renameした
2022-03-27 refactor: 要求/応答QueueをBundleでラップ
2022-03-27 feat: VirtualJtagBridge - FIFO間を実装
2022-03-27 refactor: InternalAccessCommandXXXXが長かったのでobject内に入れた
2022-03-27 test: df82688a1 のデザインがデグレしていないことを確認
2022-03-27 feat: DebugAccessTesterを実装
2022-03-27 feat: DebugAccessTesterをTopに追加
2022-03-27 fix: vjtag-fifo間のreq信号が消えていた不具合を修正 refs https://twitter.com/shino_hinaduki/status/1508173458986831880
2022-03-28 fix: カウントが進みすぎる不具合を修正
2022-03-28 fix: b5cdbd1bd の水平展開
2022-03-28 test: ShiftDRで読みだしたときの端数を消さないモードを追加
2022-03-28 fix: 切り分け用に余計な機能を削除
2022-03-28 refactor: ReadShiftDrの単位が4byte alignされていなかったので修正
2022-03-28 wip: reqTypeの分岐にswitch-isを使ったが改善せず
2022-03-28 fix: VjtagBridgeがWrite要求をアサートした直後に寝ゲーとしていた不具合を修正
2022-03-29 doc: READMEに基板の情報を追加
2022-03-29 doc: 並び順を入れ替え
2022-03-29 doc: 誤字修正
2022-03-29 refactor: board.ipのクラス名を修正(desiredNameに指定するようにした)
2022-03-29 env: diagrammer実行時のメモリを4GBに増やした
2022-03-29 doc: fix typo
2022-03-30 wip: GpioMapping.scalaを追加
2022-03-31 wip: VgaOutをTop Moduleに追加
2022-04-03 env: sbt-bloop更新
2022-04-03 fix: VGA関連のポートをUnusedで上書きして未配線になっていたので修正
2022-04-03 test: 外部からFrameBufferを書き換えるテストを追加 動作確認: https://twitter.com/shino_hinaduki/status/1510687809782226944
2022-04-03 fix: 幅設定がおかしかったので修正
2022-04-03 test: デバッグ回路のパターン出力を変更
2022-04-04 fix: 背景色を黒以外にしたときに正常に表示されない不具合を修正 (hsync, vsync時には色を出力してはいけない)
2022-04-04 test: scale動作確認
2022-04-04 refactor: カウントの先頭をActiveVideo領域になるように修正
2022-04-04 fix: DataOutが1cyc遅れていることを考慮できていなかった点を修正
2022-04-04 fix: FrameBuffer読み出しデータが返送できていなかった不具合を修正
2022-04-04 fix: ReadShiftDrでDummyWriteした数とReadした数があっていないので修正
2022-04-04 test: Read実装を修正
2022-04-04 test: Write Patternも足して動作確認
2022-04-04 feat: 転送速度、転送量を調整してもPassすることを確認
2022-04-05 refactor: unuse port定義を上部に移動
2022-04-05 test: 6b18a694b2 の動作確認OK
2022-04-05 feat: GpioMappingを実装
2022-04-05 refactor: 細かい点を修正
2022-04-06 feat: Cartridge用DPRAMのPortBを4byteに変更
2022-04-06 feat: Cartridge配線セレクタを実装
2022-04-06 test: 06cfb6235 の動作確認OK
2022-04-06 fix: コンストラクタの定義を使うように修正
2022-04-07 feat: battery-backupしているRAM用のIPを追加
2022-04-09 refactor: cart packageをboard下に移動
2022-04-09 feat: Battery保持されたRAM分のインスタンスを追加
2022-04-09 refactor: DPRAMとの接続をきれいにした
2022-04-09 test: 063e66b38a8b の動作確認OK
2022-04-09 refactor: Cartridge-GPIO間の接続もUtilityを追加
2022-04-09 test: 45a8bbae5b7 の動作確認OK
2022-04-10 feat: iNES file header転送部分を実装
2022-04-10 wip: debugAccessTargets定義を使った実装の雛形を作成
2022-04-10 refactor: AccessTargetの定義を実装順に変更
2022-04-12 feat: CartridgeのDAP側読み書きを実装
2022-04-12 feat: Mapper0の配線を実装
2022-04-12 fix: Read応答罪忘れを修正
2022-04-15 wip: Mapperの実装を切り替えられる仕組みを実装
2022-04-15 fix: RawModuleに変更してCpuClockを明示
2022-04-15 doc: コメント追加 (ループ内で生成しても良いが、必須ではないので直さない)
2022-04-18 wip: まだ最適化で消える
2022-04-18 wip: これでもうまくいかない
2022-04-19 fix: 変数名名変更漏れを修正
2022-04-19 fix: DPRAMのサイズを縮小
2022-04-19 fix: VgaOutの管理データをRGB565に変更
2022-04-19 test: VgaOutをRGB565に変えたことの動作確認OK
2022-04-19 test: VirtualCartridgeへのW/Rテストを追加 CartCommon以外は動く
2022-04-19 test: まとめてWriteしてからVerifyするパターンを追加
2022-04-20 test: テスト実装を手直し
2022-04-20 fix: 最適化抑制追加
2022-04-20 test: CartCommonのVerifyをやめる
2022-04-20 feat: 左端のLEDにiNES Headerが正しいことの確認を追加
2022-04-20 test: 8ba4320 の動作確認OK
2022-04-24 env: runMainを使うように変更
